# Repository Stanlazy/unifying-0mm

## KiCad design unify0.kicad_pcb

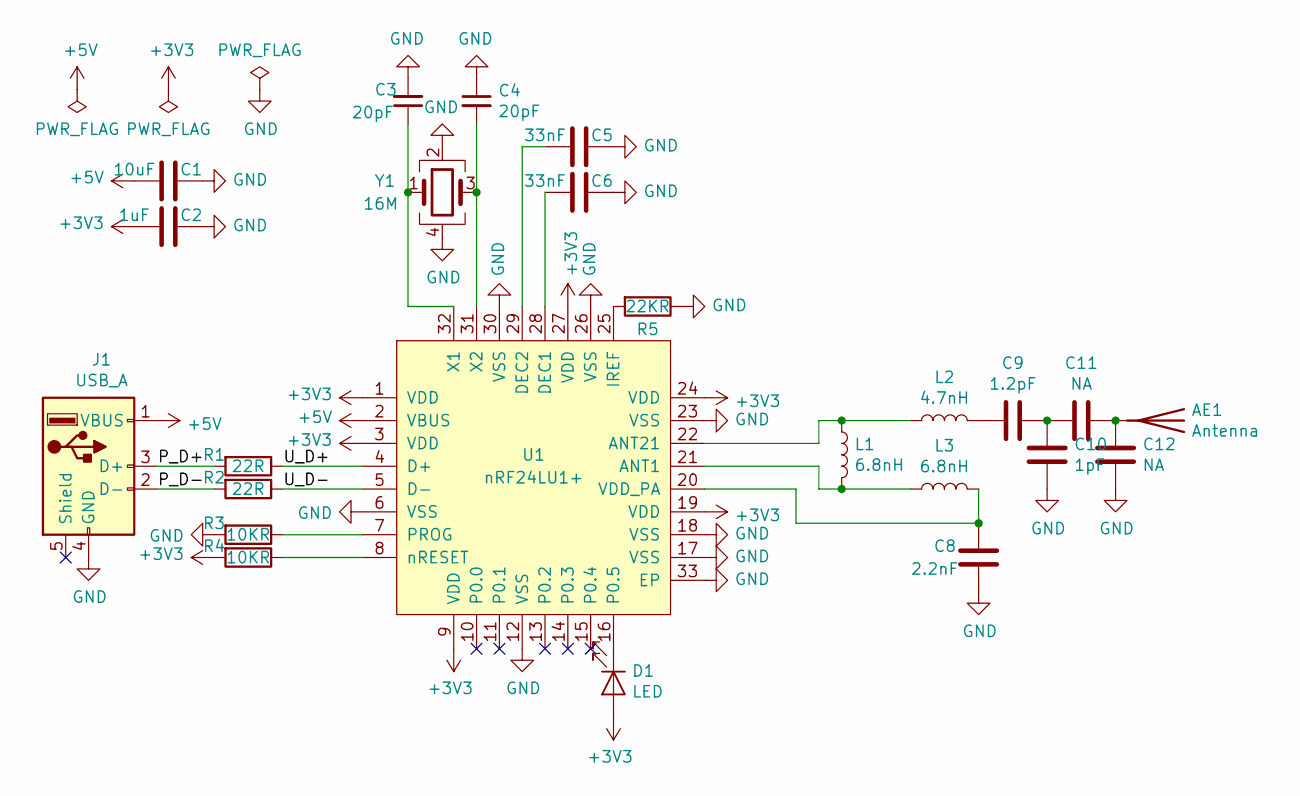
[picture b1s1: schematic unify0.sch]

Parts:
AE1: Antenna; Rainsun-AN9520
C1: 10uF; C_0201_0603Metric
C2: 1uF; C_0201_0603Metric
C3, C4: 20pF; C_0201_0603Metric
C5, C6: 33nF; C_0201_0603Metric
C8: 2.2nF; C_0201_0603Metric
C9: 1.2pF; C_0201_0603Metric
C10: 1pF; C_0201_0603Metric
C11, C12: NA; C_0201_0603Metric
D1: LED; LED_0402_1005Metric
J1: USB_A; USB_A_Onboard
L1, L3: 6.8nH; L_0201_0603Metric
L2: 4.7nH; L_0201_0603Metric
R1, R2: 22R; R_0201_0603Metric
R3, R4: 10KR; R_0201_0603Metric
R5: 22KR; R_0201_0603Metric
U1: nRF24LU1+; QFN-32-1EP_5x5mm_P0.5mm_EP3.1x3.1mm
Y1: 16M; Crystal_SMD_2016-4Pin_2.0x1.6mm

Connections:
+3V3: C2.2, D1.2 (A), R4.2, U1.1 (VDD), U1.3 (VDD), U1.9 (VDD), U1.19 (VDD), U1.24 (VDD), U1.27 (VDD)
+5V: C1.2, J1.1 (VBUS), U1.2 (VBUS)
/P_D+: J1.3 (D+), R1.2
/P_D-: J1.2 (D-), R2.2
/U_D+: R1.1, U1.4 (D+)
/U_D-: R2.1, U1.5 (D-)
GND: C1.1, C2.1, C3.2, C4.1, C5.1, C6.1, C8.2, C10.2, C12.2, J1.4 (GND), R3.2, R5.1, U1.6 (VSS), U1.12 (VSS), U1.17 (VSS), U1.18 (VSS), U1.23 (VSS), U1.26 (VSS), U1.30 (VSS), U1.33 (EP), Y1.2, Y1.4
unnamed: AE1.1, C11.1, C12.1
unnamed: C3.1, U1.32 (X1), Y1.1
unnamed: C4.2, U1.31 (X2), Y1.3
unnamed: C5.2, U1.29 (DEC2)
unnamed: C6.2, U1.28 (DEC1)
unnamed: C8.1, L3.2, U1.20 (VDD_PA)
unnamed: C9.2, L2.2
unnamed: C9.1, C10.1, C11.2
unnamed: D1.1 (K), U1.16 (P0.5)
unnamed: L1.1, L2.1, U1.22 (ANT21)
unnamed: L1.2, L3.1, U1.21 (ANT1)
unnamed: R3.1, U1.7 (PROG)
unnamed: R4.1, U1.8 (nRESET)
unnamed: R5.2, U1.25 (IREF)

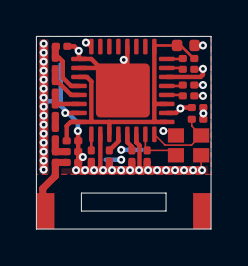
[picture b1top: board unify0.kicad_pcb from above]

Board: 4 copper layers, 9.7 x 10.7 mm, 24 parts (1 on the bottom side), 21 nets.

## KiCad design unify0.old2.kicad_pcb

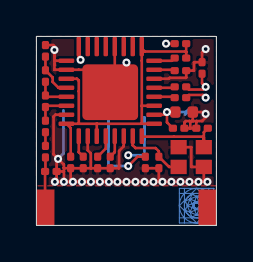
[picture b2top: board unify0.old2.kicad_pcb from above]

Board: 4 copper layers, 10.0 x 10.5 mm, 25 parts (1 on the bottom side), 20 nets.

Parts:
AE1: Antenna; Rainsun-AN9520
C1: 10uF; C_0402_1005Metric
C2, C3: 20pF; C_0201_0603Metric
C4, C5: 33nF; C_0201_0603Metric
C6: 1uF; C_0201_0603Metric
C7: 2.2nF; C_0201_0603Metric
C8: 1.2pF; C_0201_0603Metric
C9: 1pF; C_0201_0603Metric
D1, D2, D3: TPD1E6B06; R_0201_0603Metric
D4: LED; LED_0201_0603Metric
J1: USB_A; USB_A_Onboard
L1, L3: 6.8nH; L_0201_0603Metric
L2: 4.7nH; L_0201_0603Metric
R1, R2: 22R; R_0201_0603Metric
R3, R4: 10KR; R_0201_0603Metric
R5: 22KR; R_0201_0603Metric
U1: nRF24LU1+; QFN-32-1EP_5x5mm_P0.5mm_EP3.1x3.1mm
Y1: 16M; Crystal_SMD_2016-4Pin_2.0x1.6mm

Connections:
+3V3: C6.2, D4.2, R4.2, U1.1, U1.3, U1.9, U1.19, U1.24, U1.27
+5V: C1.2, D1.2, J1.1, U1.2
/P_D+: D2.2, J1.3, R1.2
/P_D-: D3.2, J1.2, R2.2
/U_D+: R1.1, U1.4
/U_D-: R2.1, U1.5
GND: C1.1, C2.2, C3.1, C4.1, C5.1, C6.1, C7.2, C9.2, D1.1, D2.1, D3.1, J1.4, R3.2, R5.1, U1.6, U1.12, U1.17, U1.18, U1.23, U1.26, U1.30, U1.33, Y1.2, Y1.4
unnamed: AE1.1, C8.1, C9.1
unnamed: C2.1, U1.32, Y1.1
unnamed: C3.2, U1.31, Y1.3
unnamed: C4.2, U1.29
unnamed: C5.2, U1.28
unnamed: C7.1, L3.2, U1.20
unnamed: C8.2, L2.2
unnamed: D4.1, U1.16
unnamed: L1.1, L2.1, U1.22
unnamed: L1.2, L3.1, U1.21
unnamed: R3.1, U1.7
unnamed: R4.1, U1.8
unnamed: R5.2, U1.25

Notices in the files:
unify0.kicad_pcb:
©Stanlazy
